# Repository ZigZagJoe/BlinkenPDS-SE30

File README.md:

68030 PDS Interposer / "BlinkenPDS" diagnostic board for SE/30/IIsi.

Top connector is a passthrough for card under test, side connector is for logic analyzer pins or a second card.
NOT intended for use in a case, though it will fit (poorly). 

BlinkenPDS (c) by zigzagjoe 2024

BlinkenPDS is licensed under a
Creative Commons Attribution-NonCommercial 4.0 International License.

You should have received a copy of the license along with this
work. If not, see <https://creativecommons.org/licenses/by-nc/4.0/>.

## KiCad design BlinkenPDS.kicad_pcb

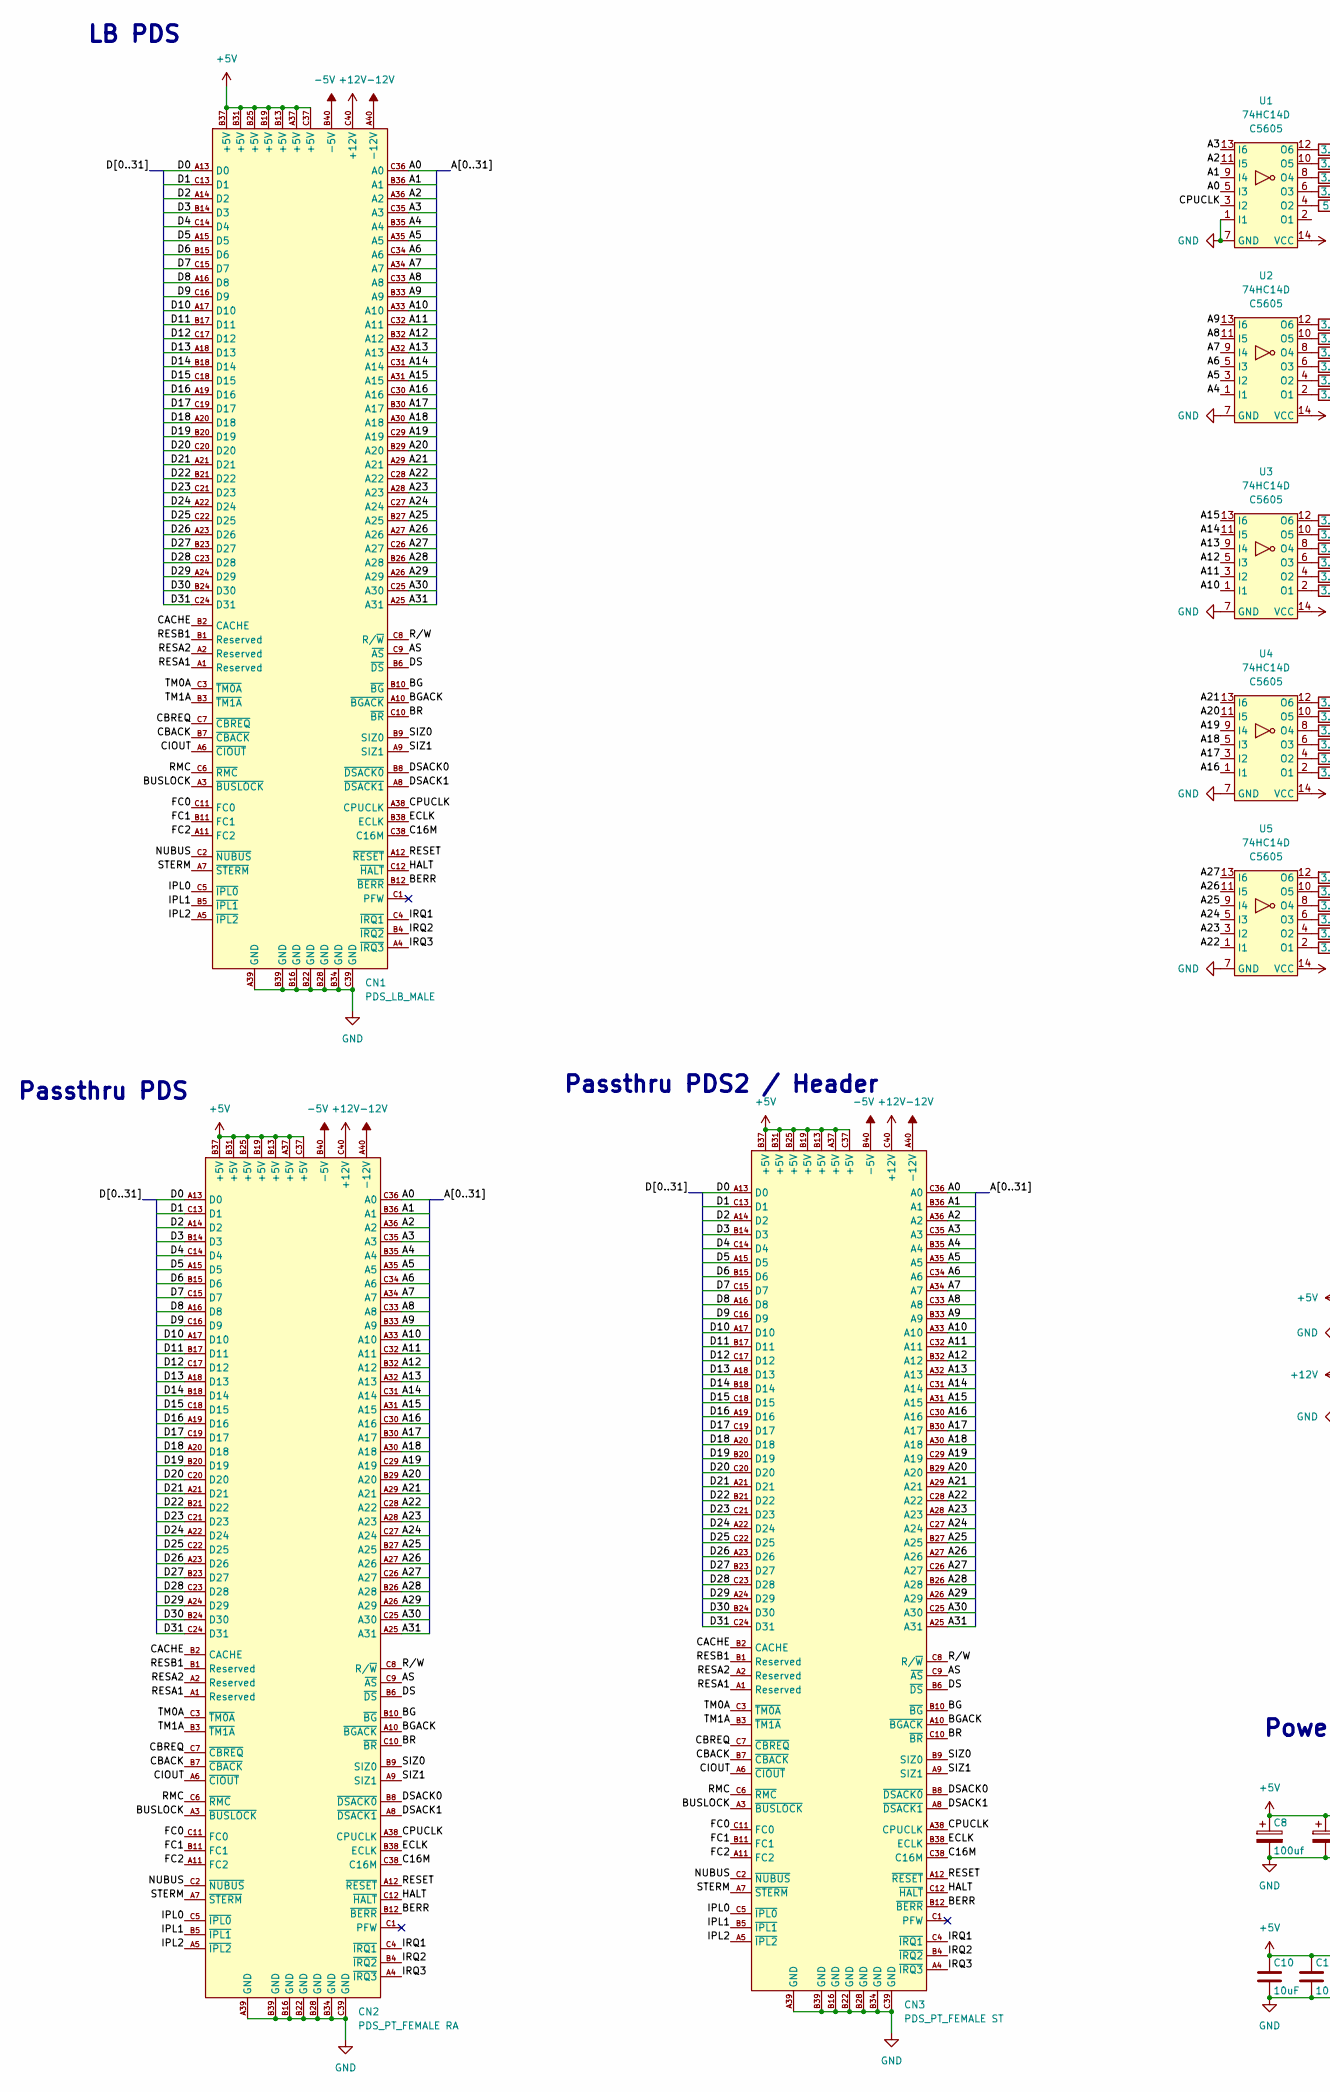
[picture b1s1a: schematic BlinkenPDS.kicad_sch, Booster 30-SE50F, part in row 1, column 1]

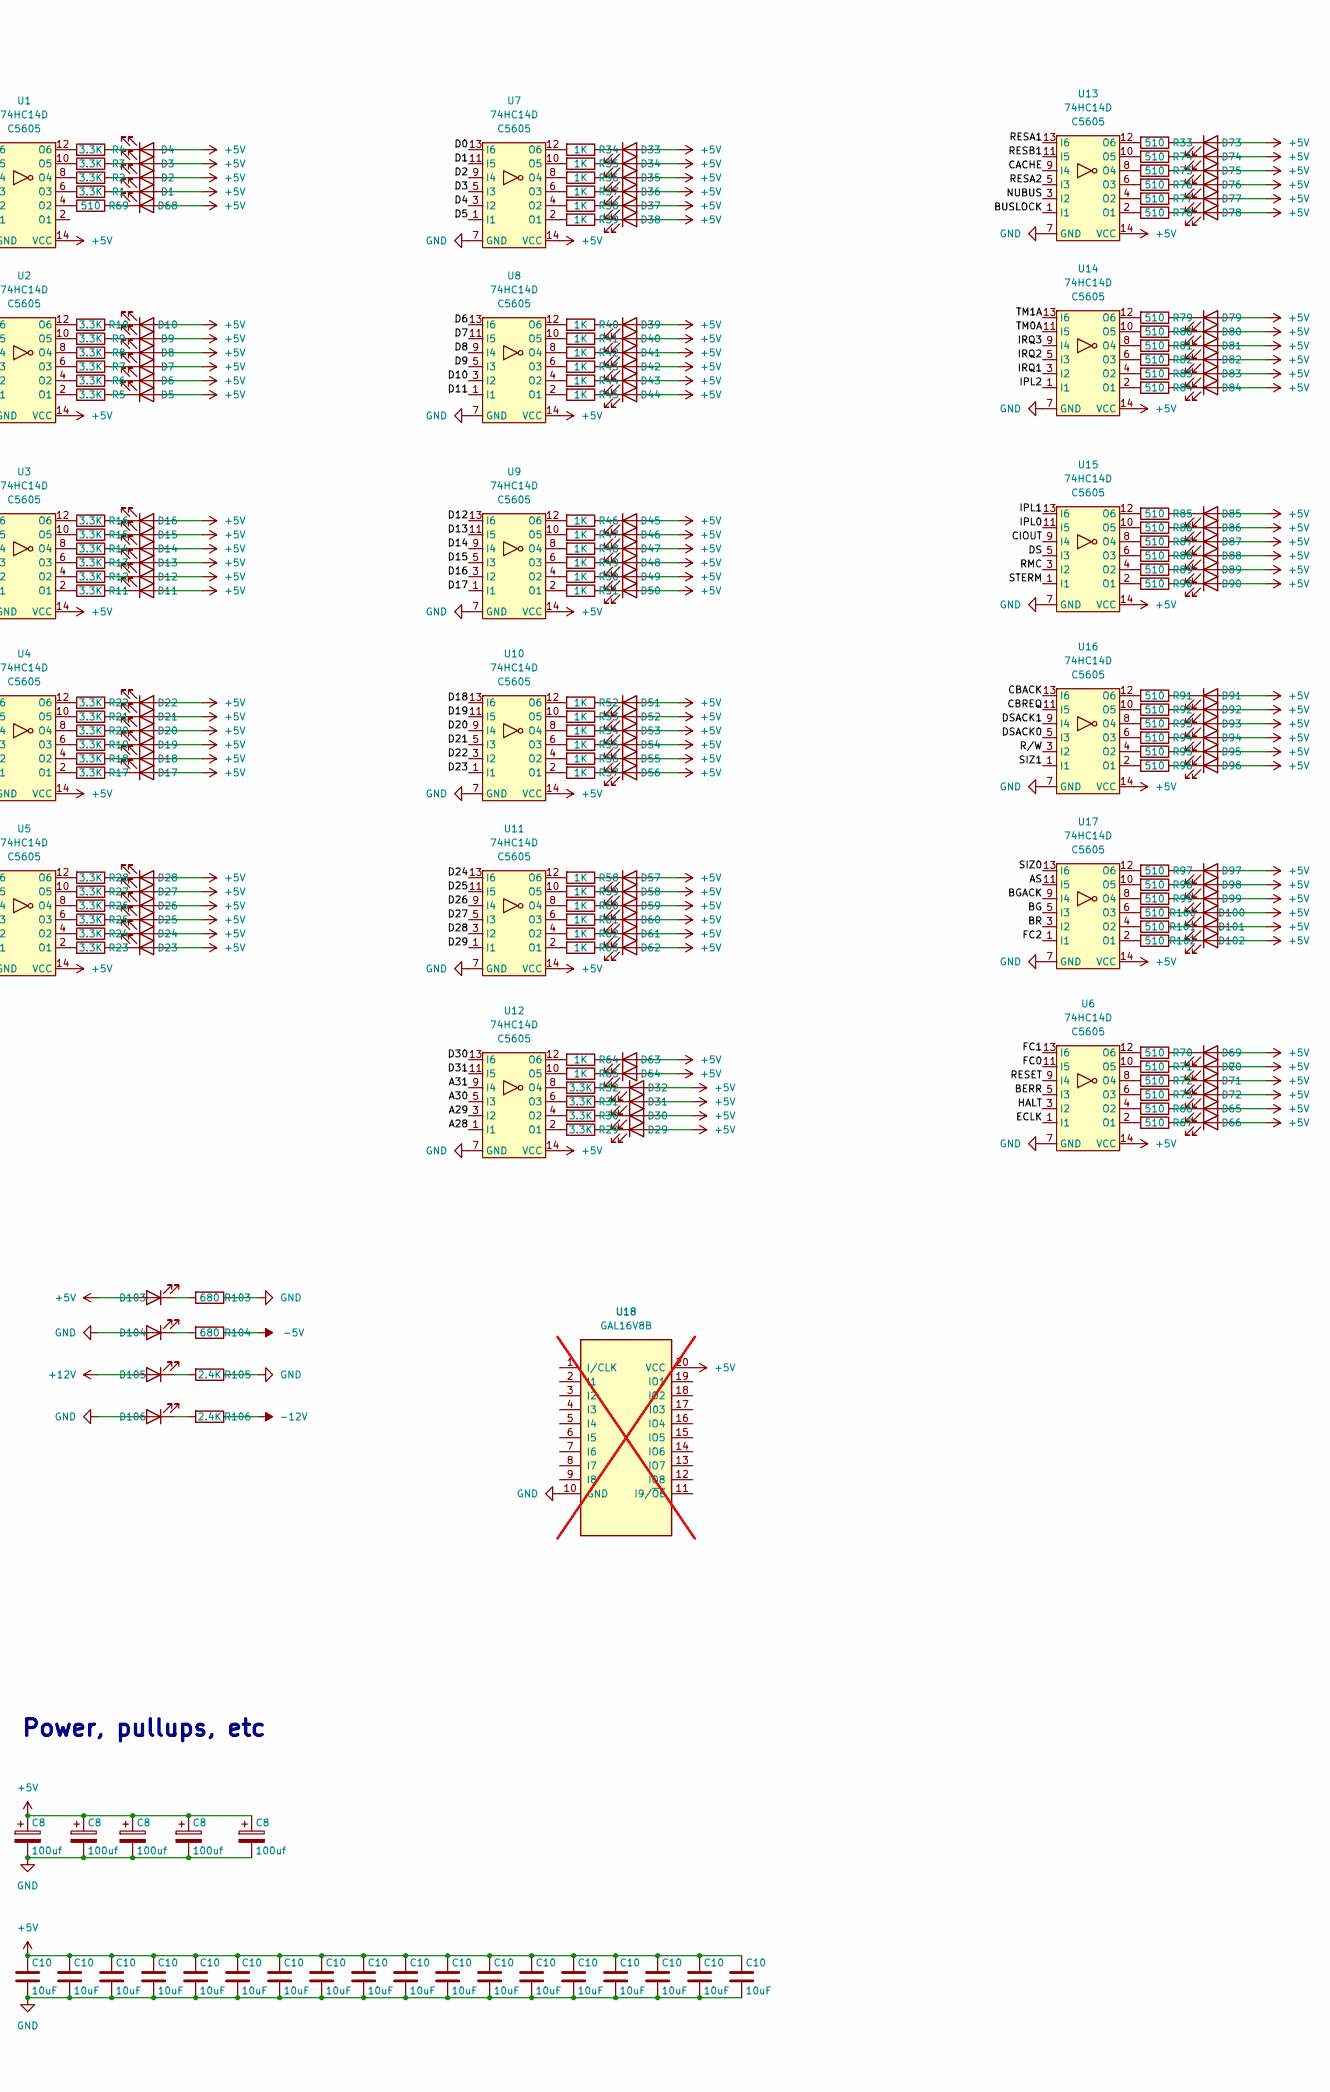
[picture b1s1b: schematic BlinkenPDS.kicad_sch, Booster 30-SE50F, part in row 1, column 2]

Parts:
C8: 100uf; CP_EIA-3528-15_AVX-H; LCSC C16133
C10: 10uF; C_0805_2012Metric; PartNumber CL21A106KPFNNNG; LCSC C15850
CN1: PDS_LB_MALE; 650949-5 RA MALE
CN2: PDS_PT_FEMALE RA; 650874-4 RA FEMALE
CN3: PDS_PT_FEMALE ST; 535098-5 ST FEMALE
D1, D2, D3, D4, D5, D6, D7, D8, D9, D10, D11, D12, D13, D14, D15, D16, D17, D18, D19, D20, D21, D22, D23, D24, D25, D26, D27, D28, D29, D30, D31, D32: A; LED_0603_1608Metric_Label; PartNumber GRN; LCSC C2986059
D33, D34, D35, D36, D37, D38, D39, D40, D41, D42, D43, D44, D45, D46, D47, D48, D49, D50, D51, D52, D53, D54, D55, D56, D57, D58, D59, D60, D61, D62, D63, D64: D; LED_0603_1608Metric_Label; PartNumber Red; LCSC C2286
D65, D66, D68, D69, D70, D71, D72, D73, D74, D75, D76, D77, D78, D79, D80, D81, D82, D83, D84, D85, D86, D87, D88, D89, D90, D91, D92, D93, D94, D95, D96, D97, D98, D99, D100, D101, D102: C; LED_0603_1608Metric_Label; PartNumber YLW; LCSC C72038
D103, D104, D105, D106: P; LED_0603_1608Metric_Label; PartNumber Blue; LCSC C2986058
R1, R2, R3, R4, R5, R6, R7, R8, R9, R10, R11, R12, R13, R14, R15, R16, R17, R18, R19, R20, R21, R22, R23, R24, R25, R26, R27, R28, R29, R30, R31, R32: 3.3K; R_0402_1005Metric_NoLabel; LCSC C25890
R33, R66, R67, R69, R70, R71, R72, R73, R74, R75, R76, R77, R78, R79, R80, R81, R82, R83, R84, R85, R86, R87, R88, R89, R90, R91, R92, R93, R94, R95, R96, R97, R98, R99, R100, R101, R102: 510; R_0402_1005Metric_NoLabel; LCSC C25123
R34, R35, R36, R37, R38, R39, R40, R41, R42, R43, R44, R45, R46, R47, R48, R49, R50, R51, R52, R53, R54, R55, R56, R57, R58, R59, R60, R61, R62, R63, R64, R65: 1K; R_0402_1005Metric_NoLabel; LCSC C25104
R103, R104: 680; R_0402_1005Metric_NoLabel; LCSC C25130
R105, R106: 2.4K; R_0402_1005Metric_NoLabel; LCSC C25882
U1, U2, U3, U4, U5, U6, U7, U8, U9, U10, U11, U12, U13, U14, U15, U16, U17: 74HC14D; SOIC-14_3.9x8.7mm_P1.27mm; LCSC C5605
U18: GAL16V8B; DIP-20_W7.62mm_Socket_LongPads; not fitted

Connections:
+5V: C8.1, C10.1, CN1.A37 (+5V), CN1.B13 (+5V), CN1.B19 (+5V), CN1.B25 (+5V), CN1.B31 (+5V), CN1.B37 (+5V), CN1.C37 (+5V), CN2.A37 (+5V), CN2.B13 (+5V), CN2.B19 (+5V), CN2.B25 (+5V), CN2.B31 (+5V), CN2.B37 (+5V), CN2.C37 (+5V), CN3.A37 (+5V), CN3.B13 (+5V), CN3.B19 (+5V), CN3.B25 (+5V), CN3.B31 (+5V), CN3.B37 (+5V), CN3.C37 (+5V), D1.2 (A), D2.2 (A), D3.2 (A), D4.2 (A), D5.2 (A), D6.2 (A), D7.2 (A), D8.2 (A), D9.2 (A), D10.2 (A), D11.2 (A), D12.2 (A), D13.2 (A), D14.2 (A), D15.2 (A), D16.2 (A), D17.2 (A), D18.2 (A), D19.2 (A), D20.2 (A), D21.2 (A), D22.2 (A), D23.2 (A), D24.2 (A), D25.2 (A), D26.2 (A), D27.2 (A), D28.2 (A), D29.2 (A), D30.2 (A), D31.2 (A), D32.2 (A), D33.2 (A), D34.2 (A), D35.2 (A), D36.2 (A), D37.2 (A), D38.2 (A), D39.2 (A), D40.2 (A), D41.2 (A), D42.2 (A), D43.2 (A), D44.2 (A), D45.2 (A), D46.2 (A), D47.2 (A), D48.2 (A), D49.2 (A), D50.2 (A), D51.2 (A), D52.2 (A), D53.2 (A), D54.2 (A), D55.2 (A), D56.2 (A), D57.2 (A), D58.2 (A), D59.2 (A), D60.2 (A), D61.2 (A), D62.2 (A), D63.2 (A), D64.2 (A), D65.2 (A), D66.2 (A), D68.2 (A), D69.2 (A), D70.2 (A), D71.2 (A), D72.2 (A), D73.2 (A), D74.2 (A), D75.2 (A), D76.2 (A), D77.2 (A), D78.2 (A), D79.2 (A), D80.2 (A), D81.2 (A), D82.2 (A), D83.2 (A), D84.2 (A), D85.2 (A), D86.2 (A), D87.2 (A), D88.2 (A), D89.2 (A), D90.2 (A), D91.2 (A), D92.2 (A), D93.2 (A), D94.2 (A), D95.2 (A), D96.2 (A), D97.2 (A), D98.2 (A), D99.2 (A), D100.2 (A), D101.2 (A), D102.2 (A), D103.2 (A), U1.14 (VCC), U2.14 (VCC), U3.14 (VCC), U4.14 (VCC), U5.14 (VCC), U6.14 (VCC), U7.14 (VCC), U8.14 (VCC), U9.14 (VCC), U10.14 (VCC), U11.14 (VCC), U12.14 (VCC), U13.14 (VCC), U14.14 (VCC), U15.14 (VCC), U16.14 (VCC), U17.14 (VCC), U18.20 (VCC); also elsewhere on the board
+12V: CN1.C40 (+12V), CN2.C40 (+12V), CN3.C40 (+12V), D105.2 (A)
-5V: CN1.B40 (-5V), CN2.B40 (-5V), CN3.B40 (-5V), R104.1
-12V: CN1.A40 (-12V), CN2.A40 (-12V), CN3.A40 (-12V), R106.1
/A0: CN1.C36 (A0), CN2.C36 (A0), CN3.C36 (A0), U1.5 (I3)
/A1: CN1.B36 (A1), CN2.B36 (A1), CN3.B36 (A1), U1.9 (I4)
/A2: CN1.A36 (A2), CN2.A36 (A2), CN3.A36 (A2), U1.11 (I5)
/A3: CN1.C35 (A3), CN2.C35 (A3), CN3.C35 (A3), U1.13 (I6)
/A4: CN1.B35 (A4), CN2.B35 (A4), CN3.B35 (A4), U2.1 (I1)
/A5: CN1.A35 (A5), CN2.A35 (A5), CN3.A35 (A5), U2.3 (I2)
/A6: CN1.C34 (A6), CN2.C34 (A6), CN3.C34 (A6), U2.5 (I3)
/A7: CN1.A34 (A7), CN2.A34 (A7), CN3.A34 (A7), U2.9 (I4)
/A8: CN1.C33 (A8), CN2.C33 (A8), CN3.C33 (A8), U2.11 (I5)
/A9: CN1.B33 (A9), CN2.B33 (A9), CN3.B33 (A9), U2.13 (I6)
/A10: CN1.A33 (A10), CN2.A33 (A10), CN3.A33 (A10), U3.1 (I1)
/A11: CN1.C32 (A11), CN2.C32 (A11), CN3.C32 (A11), U3.3 (I2)
/A12: CN1.B32 (A12), CN2.B32 (A12), CN3.B32 (A12), U3.5 (I3)
/A13: CN1.A32 (A13), CN2.A32 (A13), CN3.A32 (A13), U3.9 (I4)
/A14: CN1.C31 (A14), CN2.C31 (A14), CN3.C31 (A14), U3.11 (I5)
/A15: CN1.A31 (A15), CN2.A31 (A15), CN3.A31 (A15), U3.13 (I6)
/A16: CN1.C30 (A16), CN2.C30 (A16), CN3.C30 (A16), U4.1 (I1)
/A17: CN1.B30 (A17), CN2.B30 (A17), CN3.B30 (A17), U4.3 (I2)
/A18: CN1.A30 (A18), CN2.A30 (A18), CN3.A30 (A18), U4.5 (I3)
/A19: CN1.C29 (A19), CN2.C29 (A19), CN3.C29 (A19), U4.9 (I4)
/A20: CN1.B29 (A20), CN2.B29 (A20), CN3.B29 (A20), U4.11 (I5)
/A21: CN1.A29 (A21), CN2.A29 (A21), CN3.A29 (A21), U4.13 (I6)
/A22: CN1.C28 (A22), CN2.C28 (A22), CN3.C28 (A22), U5.1 (I1)
/A23: CN1.A28 (A23), CN2.A28 (A23), CN3.A28 (A23), U5.3 (I2)
/A24: CN1.C27 (A24), CN2.C27 (A24), CN3.C27 (A24), U5.5 (I3)
/A25: CN1.B27 (A25), CN2.B27 (A25), CN3.B27 (A25), U5.9 (I4)
/A26: CN1.A27 (A26), CN2.A27 (A26), CN3.A27 (A26), U5.11 (I5)
/A27: CN1.C26 (A27), CN2.C26 (A27), CN3.C26 (A27), U5.13 (I6)
/A28: CN1.B26 (A28), CN2.B26 (A28), CN3.B26 (A28), U12.1 (I1)
/A29: CN1.A26 (A29), CN2.A26 (A29), CN3.A26 (A29), U12.3 (I2)
/A30: CN1.C25 (A30), CN2.C25 (A30), CN3.C25 (A30), U12.5 (I3)
/A31: CN1.A25 (A31), CN2.A25 (A31), CN3.A25 (A31), U12.9 (I4)
/AS: CN1.C9 (~AS), CN2.C9 (~AS), CN3.C9 (~AS), U17.11 (I5)
/BERR: CN1.B12 (~BERR), CN2.B12 (~BERR), CN3.B12 (~BERR), U6.5 (I3)
/BG: CN1.B10 (~BG), CN2.B10 (~BG), CN3.B10 (~BG), U17.5 (I3)
/BGACK: CN1.A10 (~BGACK), CN2.A10 (~BGACK), CN3.A10 (~BGACK), U17.9 (I4)
/BR: CN1.C10 (~BR), CN2.C10 (~BR), CN3.C10 (~BR), U17.3 (I2)
/BUSLOCK: CN1.A3 (~BUSLOCK), CN2.A3 (~BUSLOCK), CN3.A3 (~BUSLOCK), U13.1 (I1)
/C16M: CN1.C38 (C16M), CN2.C38 (C16M), CN3.C38 (C16M)
/CACHE: CN1.B2 (CACHE), CN2.B2 (CACHE), CN3.B2 (CACHE), U13.9 (I4)
/CBACK: CN1.B7 (~CBACK), CN2.B7 (~CBACK), CN3.B7 (~CBACK), U16.13 (I6)
/CBREQ: CN1.C7 (~CBREQ), CN2.C7 (~CBREQ), CN3.C7 (~CBREQ), U16.11 (I5)
/CIOUT: CN1.A6 (~CIOUT), CN2.A6 (~CIOUT), CN3.A6 (~CIOUT), U15.9 (I4)
/CPUCLK: CN1.A38 (CPUCLK), CN2.A38 (CPUCLK), CN3.A38 (CPUCLK), U1.3 (I2)
/D0: CN1.A13 (D0), CN2.A13 (D0), CN3.A13 (D0), U7.13 (I6)
/D1: CN1.C13 (D1), CN2.C13 (D1), CN3.C13 (D1), U7.11 (I5)
/D2: CN1.A14 (D2), CN2.A14 (D2), CN3.A14 (D2), U7.9 (I4)
/D3: CN1.B14 (D3), CN2.B14 (D3), CN3.B14 (D3), U7.5 (I3)
/D4: CN1.C14 (D4), CN2.C14 (D4), CN3.C14 (D4), U7.3 (I2)
/D5: CN1.A15 (D5), CN2.A15 (D5), CN3.A15 (D5), U7.1 (I1)
/D6: CN1.B15 (D6), CN2.B15 (D6), CN3.B15 (D6), U8.13 (I6)
/D7: CN1.C15 (D7), CN2.C15 (D7), CN3.C15 (D7), U8.11 (I5)
/D8: CN1.A16 (D8), CN2.A16 (D8), CN3.A16 (D8), U8.9 (I4)
/D9: CN1.C16 (D9), CN2.C16 (D9), CN3.C16 (D9), U8.5 (I3)
/D10: CN1.A17 (D10), CN2.A17 (D10), CN3.A17 (D10), U8.3 (I2)
/D11: CN1.B17 (D11), CN2.B17 (D11), CN3.B17 (D11), U8.1 (I1)
/D12: CN1.C17 (D12), CN2.C17 (D12), CN3.C17 (D12), U9.13 (I6)
/D13: CN1.A18 (D13), CN2.A18 (D13), CN3.A18 (D13), U9.11 (I5)
/D14: CN1.B18 (D14), CN2.B18 (D14), CN3.B18 (D14), U9.9 (I4)
/D15: CN1.C18 (D15), CN2.C18 (D15), CN3.C18 (D15), U9.5 (I3)
/D16: CN1.A19 (D16), CN2.A19 (D16), CN3.A19 (D16), U9.3 (I2)
/D17: CN1.C19 (D17), CN2.C19 (D17), CN3.C19 (D17), U9.1 (I1)
/D18: CN1.A20 (D18), CN2.A20 (D18), CN3.A20 (D18), U10.13 (I6)
/D19: CN1.B20 (D19), CN2.B20 (D19), CN3.B20 (D19), U10.11 (I5)
/D20: CN1.C20 (D20), CN2.C20 (D20), CN3.C20 (D20), U10.9 (I4)
/D21: CN1.A21 (D21), CN2.A21 (D21), CN3.A21 (D21), U10.5 (I3)
/D22: CN1.B21 (D22), CN2.B21 (D22), CN3.B21 (D22), U10.3 (I2)
/D23: CN1.C21 (D23), CN2.C21 (D23), CN3.C21 (D23), U10.1 (I1)
/D24: CN1.A22 (D24), CN2.A22 (D24), CN3.A22 (D24), U11.13 (I6)
/D25: CN1.C22 (D25), CN2.C22 (D25), CN3.C22 (D25), U11.11 (I5)
/D26: CN1.A23 (D26), CN2.A23 (D26), CN3.A23 (D26), U11.9 (I4)
/D27: CN1.B23 (D27), CN2.B23 (D27), CN3.B23 (D27), U11.5 (I3)
/D28: CN1.C23 (D28), CN2.C23 (D28), CN3.C23 (D28), U11.3 (I2)
/D29: CN1.A24 (D29), CN2.A24 (D29), CN3.A24 (D29), U11.1 (I1)
/D30: CN1.B24 (D30), CN2.B24 (D30), CN3.B24 (D30), U12.13 (I6)
/D31: CN1.C24 (D31), CN2.C24 (D31), CN3.C24 (D31), U12.11 (I5)
/DS: CN1.B6 (~DS), CN2.B6 (~DS), CN3.B6 (~DS), U15.5 (I3)
/DSACK0: CN1.B8 (~DSACK0), CN2.B8 (~DSACK0), CN3.B8 (~DSACK0), U16.5 (I3)
/DSACK1: CN1.A8 (~DSACK1), CN2.A8 (~DSACK1), CN3.A8 (~DSACK1), U16.9 (I4)
/ECLK: CN1.B38 (ECLK), CN2.B38 (ECLK), CN3.B38 (ECLK), U6.1 (I1)
/FC0: CN1.C11 (FC0), CN2.C11 (FC0), CN3.C11 (FC0), U6.11 (I5)
/FC1: CN1.B11 (FC1), CN2.B11 (FC1), CN3.B11 (FC1), U6.13 (I6)
/FC2: CN1.A11 (FC2), CN2.A11 (FC2), CN3.A11 (FC2), U17.1 (I1)
/HALT: CN1.C12 (~HALT), CN2.C12 (~HALT), CN3.C12 (~HALT), U6.3 (I2)
/IPL0: CN1.C5 (~IPL0), CN2.C5 (~IPL0), CN3.C5 (~IPL0), U15.11 (I5)
/IPL1: CN1.B5 (~IPL1), CN2.B5 (~IPL1), CN3.B5 (~IPL1), U15.13 (I6)
/IPL2: CN1.A5 (~IPL2), CN2.A5 (~IPL2), CN3.A5 (~IPL2), U14.1 (I1)
/IRQ1: CN1.C4 (~IRQ1), CN2.C4 (~IRQ1), CN3.C4 (~IRQ1), U14.3 (I2)
/IRQ2: CN1.B4 (~IRQ2), CN2.B4 (~IRQ2), CN3.B4 (~IRQ2), U14.5 (I3)
/IRQ3: CN1.A4 (~IRQ3), CN2.A4 (~IRQ3), CN3.A4 (~IRQ3), U14.9 (I4)
/NUBUS: CN1.C2 (~NUBUS), CN2.C2 (~NUBUS), CN3.C2 (~NUBUS), U13.3 (I2)
/RESA1: CN1.A1 (Reserved), CN2.A1 (Reserved), CN3.A1 (Reserved), U13.13 (I6)
/RESA2: CN1.A2 (Reserved), CN2.A2 (Reserved), CN3.A2 (Reserved), U13.5 (I3)
/RESB1: CN1.B1 (Reserved), CN2.B1 (Reserved), CN3.B1 (Reserved), U13.11 (I5)
/RESET: CN1.A12 (~RESET), CN2.A12 (~RESET), CN3.A12 (~RESET), U6.9 (I4)
/RMC: CN1.C6 (~RMC), CN2.C6 (~RMC), CN3.C6 (~RMC), U15.3 (I2)
/R/W: CN1.C8 (R/~W), CN2.C8 (R/~W), CN3.C8 (R/~W), U16.3 (I2)
/SIZ0: CN1.B9 (SIZ0), CN2.B9 (SIZ0), CN3.B9 (SIZ0), U17.13 (I6)
/SIZ1: CN1.A9 (SIZ1), CN2.A9 (SIZ1), CN3.A9 (SIZ1), U16.1 (I1)
/STERM: CN1.A7 (~STERM), CN2.A7 (~STERM), CN3.A7 (~STERM), U15.1 (I1)
/TM0A: CN1.C3 (~TM0A), CN2.C3 (~TM0A), CN3.C3 (~TM0A), U14.11 (I5)
/TM1A: CN1.B3 (~TM1A), CN2.B3 (~TM1A), CN3.B3 (~TM1A), U14.13 (I6)
GND: C8.2, C10.2, CN1.A39 (GND), CN1.B16 (GND), CN1.B22 (GND), CN1.B28 (GND), CN1.B34 (GND), CN1.B39 (GND), CN1.C39 (GND), CN2.A39 (GND), CN2.B16 (GND), CN2.B22 (GND), CN2.B28 (GND), CN2.B34 (GND), CN2.B39 (GND), CN2.C39 (GND), CN3.A39 (GND), CN3.B16 (GND), CN3.B22 (GND), CN3.B28 (GND), CN3.B34 (GND), CN3.B39 (GND), CN3.C39 (GND), D104.2 (A), D106.2 (A), R103.1, R105.1, U1.1 (I1), U1.7 (GND), U2.7 (GND), U3.7 (GND), U4.7 (GND), U5.7 (GND), U6.7 (GND), U7.7 (GND), U8.7 (GND), U9.7 (GND), U10.7 (GND), U11.7 (GND), U12.7 (GND), U13.7 (GND), U14.7 (GND), U15.7 (GND), U16.7 (GND), U17.7 (GND), U18.10 (GND); also elsewhere on the board
unnamed: D1.1 (K), R1.1
unnamed: D2.1 (K), R2.1
unnamed: D3.1 (K), R3.1
unnamed: D4.1 (K), R4.1
unnamed: D5.1 (K), R5.1
unnamed: D6.1 (K), R6.1
unnamed: D7.1 (K), R7.1
unnamed: D8.1 (K), R8.1
unnamed: D9.1 (K), R9.1
unnamed: D10.1 (K), R10.1
unnamed: D11.1 (K), R11.1
unnamed: D12.1 (K), R12.1
unnamed: D13.1 (K), R13.1
unnamed: D14.1 (K), R14.1
unnamed: D15.1 (K), R15.1
unnamed: D16.1 (K), R16.1
unnamed: D17.1 (K), R17.1
unnamed: D18.1 (K), R18.1
unnamed: D19.1 (K), R19.1
unnamed: D20.1 (K), R20.1
unnamed: D21.1 (K), R21.1
unnamed: D22.1 (K), R22.1
unnamed: D23.1 (K), R23.1
unnamed: D24.1 (K), R24.1
unnamed: D25.1 (K), R25.1
unnamed: D26.1 (K), R26.1
unnamed: D27.1 (K), R27.1
unnamed: D28.1 (K), R28.1
unnamed: D29.1 (K), R29.1
unnamed: D30.1 (K), R30.1
unnamed: D31.1 (K), R31.1
unnamed: D32.1 (K), R32.1
unnamed: D33.1 (K), R34.1
unnamed: D34.1 (K), R35.1
unnamed: D35.1 (K), R36.1
unnamed: D36.1 (K), R37.1
unnamed: D37.1 (K), R38.1
unnamed: D38.1 (K), R39.1
unnamed: D39.1 (K), R40.1
unnamed: D40.1 (K), R41.1
unnamed: D41.1 (K), R42.1
unnamed: D42.1 (K), R43.1
unnamed: D43.1 (K), R44.1
unnamed: D44.1 (K), R45.1
unnamed: D45.1 (K), R46.1
unnamed: D46.1 (K), R47.1
unnamed: D47.1 (K), R48.1
unnamed: D48.1 (K), R49.1
unnamed: D49.1 (K), R50.1
unnamed: D50.1 (K), R51.1
unnamed: D51.1 (K), R52.1
unnamed: D52.1 (K), R53.1
unnamed: D53.1 (K), R54.1
unnamed: D54.1 (K), R55.1
unnamed: D55.1 (K), R56.1
unnamed: D56.1 (K), R57.1
unnamed: D57.1 (K), R58.1
unnamed: D58.1 (K), R59.1
unnamed: D59.1 (K), R60.1
unnamed: D60.1 (K), R61.1
unnamed: D61.1 (K), R62.1
unnamed: D62.1 (K), R63.1
unnamed: D63.1 (K), R64.1
unnamed: D64.1 (K), R65.1
unnamed: D65.1 (K), R66.1
unnamed: D66.1 (K), R67.1
unnamed: D68.1 (K), R69.1
unnamed: D69.1 (K), R70.1
unnamed: D70.1 (K), R71.1
unnamed: D71.1 (K), R72.1
unnamed: D72.1 (K), R73.1
unnamed: D73.1 (K), R33.1
unnamed: D74.1 (K), R74.1
unnamed: D75.1 (K), R75.1
unnamed: D76.1 (K), R76.1
unnamed: D77.1 (K), R77.1
unnamed: D78.1 (K), R78.1
unnamed: D79.1 (K), R79.1
unnamed: D80.1 (K), R80.1
unnamed: D81.1 (K), R81.1
unnamed: D82.1 (K), R82.1
unnamed: D83.1 (K), R83.1
unnamed: D84.1 (K), R84.1
unnamed: D85.1 (K), R85.1
unnamed: D86.1 (K), R86.1
unnamed: D87.1 (K), R87.1
unnamed: D88.1 (K), R88.1
unnamed: D89.1 (K), R89.1
unnamed: D90.1 (K), R90.1
unnamed: D91.1 (K), R91.1
unnamed: D92.1 (K), R92.1
unnamed: D93.1 (K), R93.1
unnamed: D94.1 (K), R94.1
unnamed: D95.1 (K), R95.1
unnamed: D96.1 (K), R96.1
unnamed: D97.1 (K), R97.1
unnamed: D98.1 (K), R98.1
unnamed: D99.1 (K), R99.1
unnamed: D100.1 (K), R100.1
unnamed: D101.1 (K), R101.1
unnamed: D102.1 (K), R102.1
unnamed: D103.1 (K), R103.2
unnamed: D104.1 (K), R104.2
unnamed: D105.1 (K), R105.2
unnamed: D106.1 (K), R106.2
unnamed: R69.2, U1.4 (O2)
unnamed: R1.2, U1.6 (O3)
unnamed: R2.2, U1.8 (O4)
unnamed: R3.2, U1.10 (O5)
unnamed: R4.2, U1.12 (O6)
unnamed: R5.2, U2.2 (O1)
unnamed: R6.2, U2.4 (O2)
unnamed: R7.2, U2.6 (O3)
unnamed: R8.2, U2.8 (O4)
unnamed: R9.2, U2.10 (O5)
unnamed: R10.2, U2.12 (O6)
unnamed: R11.2, U3.2 (O1)
unnamed: R12.2, U3.4 (O2)
unnamed: R13.2, U3.6 (O3)
unnamed: R14.2, U3.8 (O4)
unnamed: R15.2, U3.10 (O5)
unnamed: R16.2, U3.12 (O6)
unnamed: R17.2, U4.2 (O1)
unnamed: R18.2, U4.4 (O2)
unnamed: R19.2, U4.6 (O3)
unnamed: R20.2, U4.8 (O4)
unnamed: R21.2, U4.10 (O5)
unnamed: R22.2, U4.12 (O6)
unnamed: R23.2, U5.2 (O1)
unnamed: R24.2, U5.4 (O2)
unnamed: R25.2, U5.6 (O3)
unnamed: R26.2, U5.8 (O4)
unnamed: R27.2, U5.10 (O5)
unnamed: R28.2, U5.12 (O6)
unnamed: R67.2, U6.2 (O1)
unnamed: R66.2, U6.4 (O2)
unnamed: R73.2, U6.6 (O3)
unnamed: R72.2, U6.8 (O4)
unnamed: R71.2, U6.10 (O5)
unnamed: R70.2, U6.12 (O6)
unnamed: R39.2, U7.2 (O1)
unnamed: R38.2, U7.4 (O2)
unnamed: R37.2, U7.6 (O3)
unnamed: R36.2, U7.8 (O4)
unnamed: R35.2, U7.10 (O5)
unnamed: R34.2, U7.12 (O6)
unnamed: R45.2, U8.2 (O1)
unnamed: R44.2, U8.4 (O2)
unnamed: R43.2, U8.6 (O3)
unnamed: R42.2, U8.8 (O4)
unnamed: R41.2, U8.10 (O5)
unnamed: R40.2, U8.12 (O6)
unnamed: R51.2, U9.2 (O1)
unnamed: R50.2, U9.4 (O2)
unnamed: R49.2, U9.6 (O3)
unnamed: R48.2, U9.8 (O4)
unnamed: R47.2, U9.10 (O5)
unnamed: R46.2, U9.12 (O6)
unnamed: R57.2, U10.2 (O1)
unnamed: R56.2, U10.4 (O2)
unnamed: R55.2, U10.6 (O3)
unnamed: R54.2, U10.8 (O4)
unnamed: R53.2, U10.10 (O5)
unnamed: R52.2, U10.12 (O6)
unnamed: R63.2, U11.2 (O1)
unnamed: R62.2, U11.4 (O2)
unnamed: R61.2, U11.6 (O3)
unnamed: R60.2, U11.8 (O4)
unnamed: R59.2, U11.10 (O5)
unnamed: R58.2, U11.12 (O6)
unnamed: R29.2, U12.2 (O1)
unnamed: R30.2, U12.4 (O2)
unnamed: R31.2, U12.6 (O3)
unnamed: R32.2, U12.8 (O4)
unnamed: R65.2, U12.10 (O5)
unnamed: R64.2, U12.12 (O6)
unnamed: R78.2, U13.2 (O1)
unnamed: R77.2, U13.4 (O2)
unnamed: R76.2, U13.6 (O3)
unnamed: R75.2, U13.8 (O4)
unnamed: R74.2, U13.10 (O5)
unnamed: R33.2, U13.12 (O6)
unnamed: R84.2, U14.2 (O1)
unnamed: R83.2, U14.4 (O2)
unnamed: R82.2, U14.6 (O3)
unnamed: R81.2, U14.8 (O4)
unnamed: R80.2, U14.10 (O5)
unnamed: R79.2, U14.12 (O6)
unnamed: R90.2, U15.2 (O1)
unnamed: R89.2, U15.4 (O2)
unnamed: R88.2, U15.6 (O3)
unnamed: R87.2, U15.8 (O4)
unnamed: R86.2, U15.10 (O5)
unnamed: R85.2, U15.12 (O6)
unnamed: R96.2, U16.2 (O1)
unnamed: R95.2, U16.4 (O2)
unnamed: R94.2, U16.6 (O3)
unnamed: R93.2, U16.8 (O4)
unnamed: R92.2, U16.10 (O5)
unnamed: R91.2, U16.12 (O6)
unnamed: R102.2, U17.2 (O1)
unnamed: R101.2, U17.4 (O2)
unnamed: R100.2, U17.6 (O3)
unnamed: R99.2, U17.8 (O4)
unnamed: R98.2, U17.10 (O5)
unnamed: R97.2, U17.12 (O6)

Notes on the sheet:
Passthru PDS
Power, pullups, etc
LB PDS
Passthru PDS2 / Header

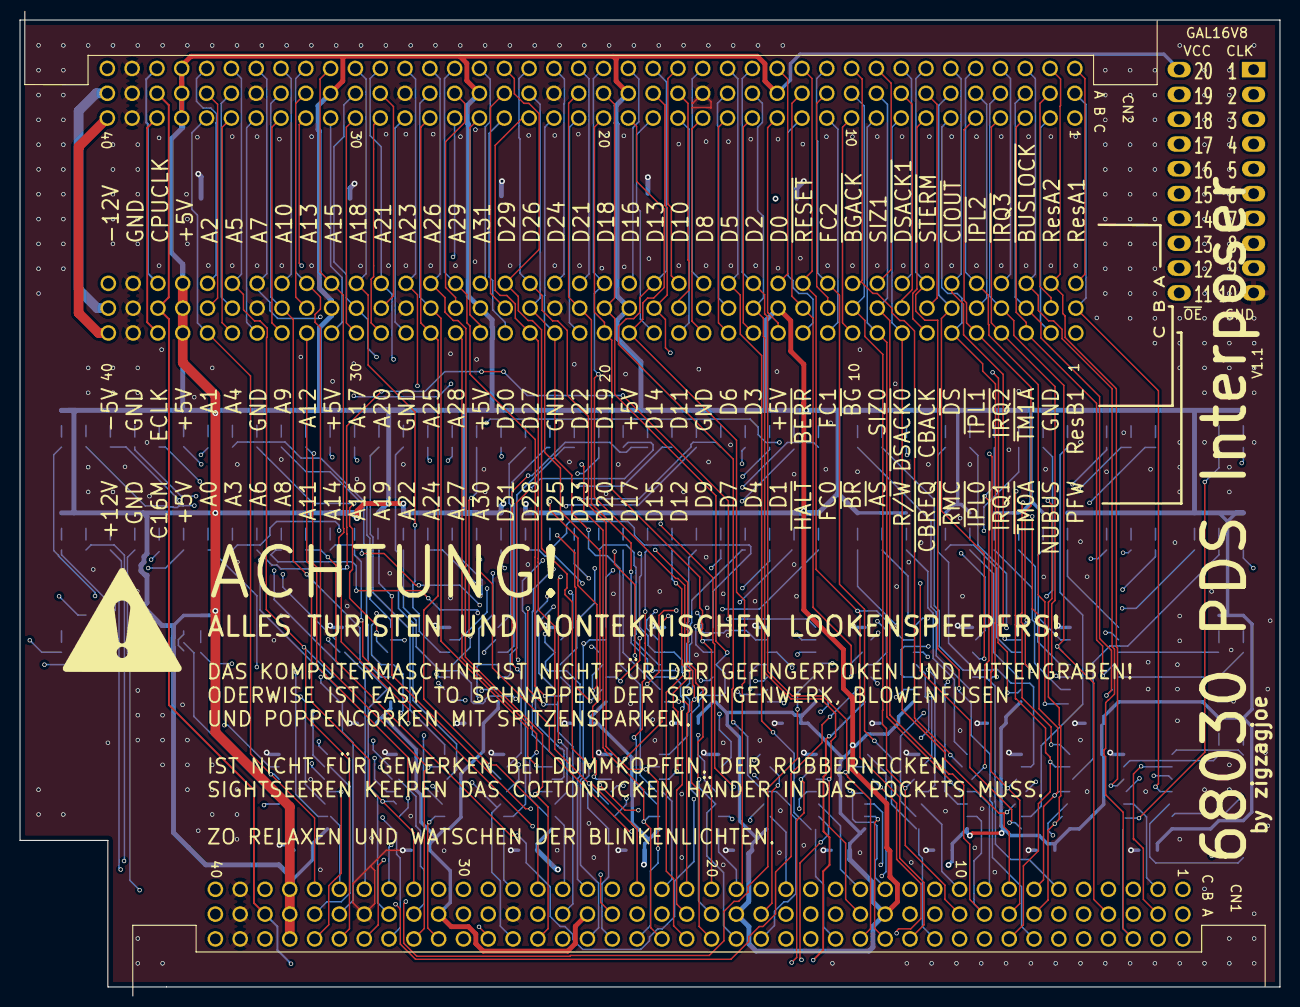
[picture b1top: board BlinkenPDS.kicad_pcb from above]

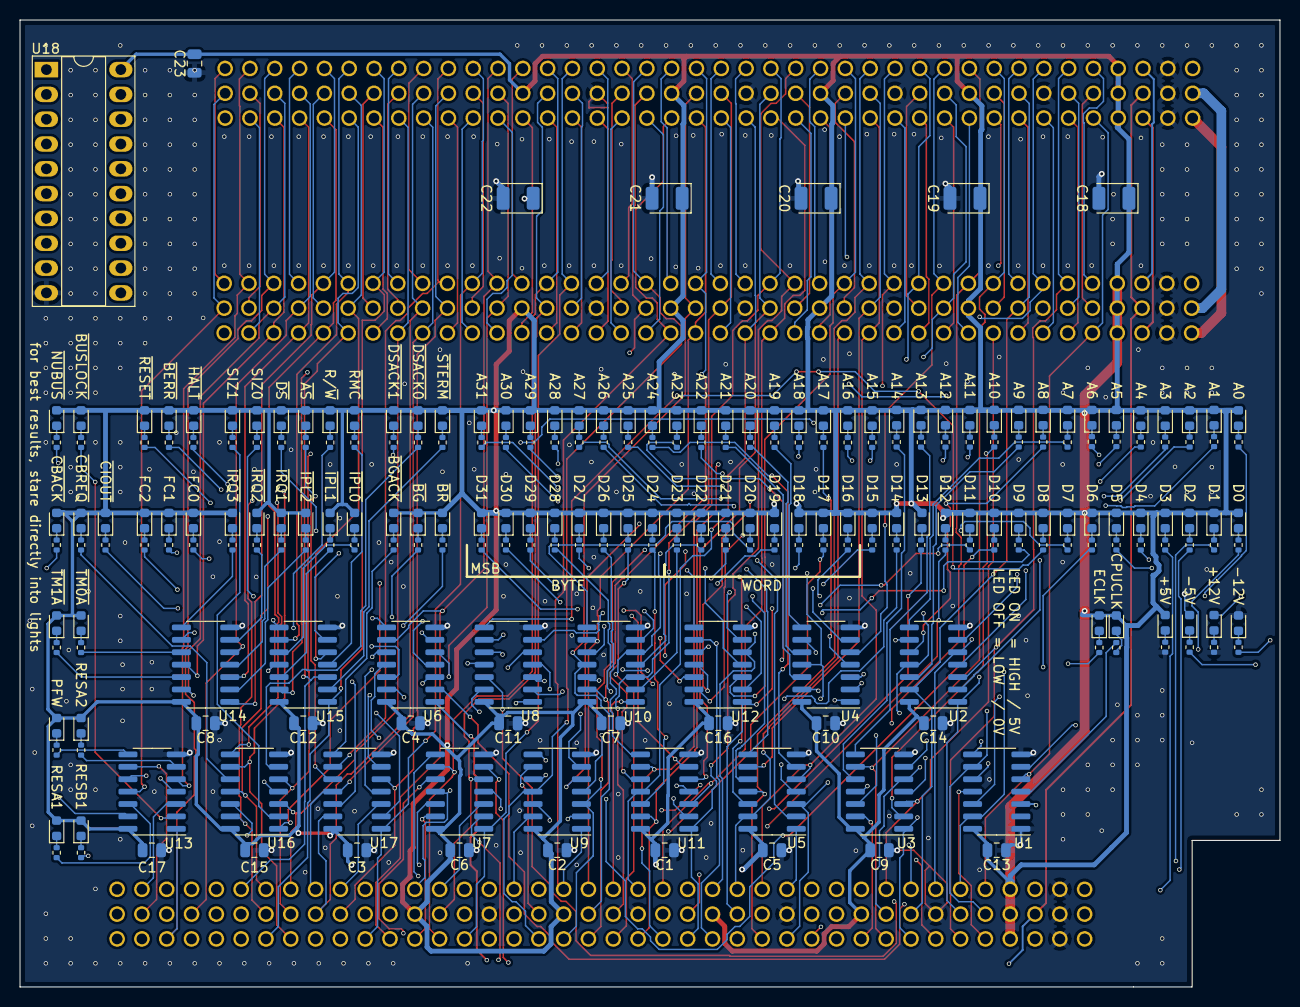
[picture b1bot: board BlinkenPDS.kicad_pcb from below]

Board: 4 copper layers, 129.0 x 99.0 mm, 254 parts (251 on the bottom side), 313 nets.

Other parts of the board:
C1, C2, C3, C4, C5, C6, C7, C9, C11, C12, C13, C14, C15, C16, C17, C23: 10uF; C_0805_2012Metric
C18, C19, C20, C21, C22: 100uf; CP_EIA-3528-15_AVX-H

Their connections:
+5V: C1.1, C2.1, C3.1, C4.1, C5.1, C6.1, C7.1, C9.1, C11.1, C12.1, C13.1, C14.1, C15.1, C16.1, C17.1, C18.1, C19.1, C20.1, C21.1, C22.1, C23.1; also elsewhere on the board
GND: C1.2, C2.2, C3.2, C4.2, C5.2, C6.2, C7.2, C9.2, C11.2, C12.2, C13.2, C14.2, C15.2, C16.2, C17.2, C18.2, C19.2, C20.2, C21.2, C22.2, C23.2; also elsewhere on the board

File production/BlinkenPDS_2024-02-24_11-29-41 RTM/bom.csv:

Designator,Footprint,Quantity,Value,LCSC Part #
"C1, C10, C11, C12, C13, C14, C15, C16, C17, C2, C23, C3, C4, C5, C6, C7, C8, C9",0805,18,10uF,C15850
"C18, C19, C20, C21, C22",CP_EIA-3528-15_AVX-H,5,100uf,C16133
CN1,650949-5 RA MALE,1,PDS_LB_MALE,
CN2,650874-4 RA FEMALE,1,PDS_PT_FEMALE RA,
CN3,535098-5 ST FEMALE,1,PDS_PT_FEMALE ST,
"D1, D10, D11, D12, D13, D14, D15, D16, D17, D18, D19, D2, D20, D21, D22, D23, D24, D25, D26, D27, D28, D29, D3, D30, D31, D32, D4, D5, D6, D7, D8, D9",0603,32,A,C2986059
"D100, D101, D102, D65, D66, D67, D68, D69, D70, D71, D72, D73, D74, D75, D76, D77, D78, D79, D80, D81, D82, D83, D84, D85, D86, D87, D88, D89, D90, D91, D92, D93, D94, D95, D96, D97, D98, D99",0603,38,C,C72038
"D103, D104, D105, D106",0603,4,P,C2986058
"D33, D34, D35, D36, D37, D38, D39, D40, D41, D42, D43, D44, D45, D46, D47, D48, D49, D50, D51, D52, D53, D54, D55, D56, D57, D58, D59, D60, D61, D62, D63, D64",0603,32,D,C2286
"R1, R10, R11, R12, R13, R14, R15, R16, R17, R18, R19, R2, R20, R21, R22, R23, R24, R25, R26, R27, R28, R29, R3, R30, R31, R32, R4, R5, R6, R7, R8, R9",0402,32,3.3K,C25890
"R100, R101, R102, R33, R66, R67, R68, R69, R70, R71, R72, R73, R74, R75, R76, R77, R78, R79, R80, R81, R82, R83, R84, R85, R86, R87, R88, R89, R90, R91, R92, R93, R94, R95, R96, R97, R98, R99",0402,38,510,C25123
"R103, R104",0402,2,680,C25130
"R105, R106",0402,2,2.4K,C25882
"R34, R35, R36, R37, R38, R39, R40, R41, R42, R43, R44, R45, R46, R47, R48, R49, R50, R51, R52, R53, R54, R55, R56, R57, R58, R59, R60, R61, R62, R63, R64, R65",0402,32,1K,C25104
"U1, U10, U11, U12, U13, U14, U15, U16, U17, U2, U3, U4, U5, U6, U7, U8, U9",SOIC-14_3.9x8.7mm_P1.27mm,17,74HC14D,C5605
U18,DIP-20_W7.62mm_Socket_LongPads,1,GAL16V8B,

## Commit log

2025-04-14 remove PFW, add CACHE, updated production files
